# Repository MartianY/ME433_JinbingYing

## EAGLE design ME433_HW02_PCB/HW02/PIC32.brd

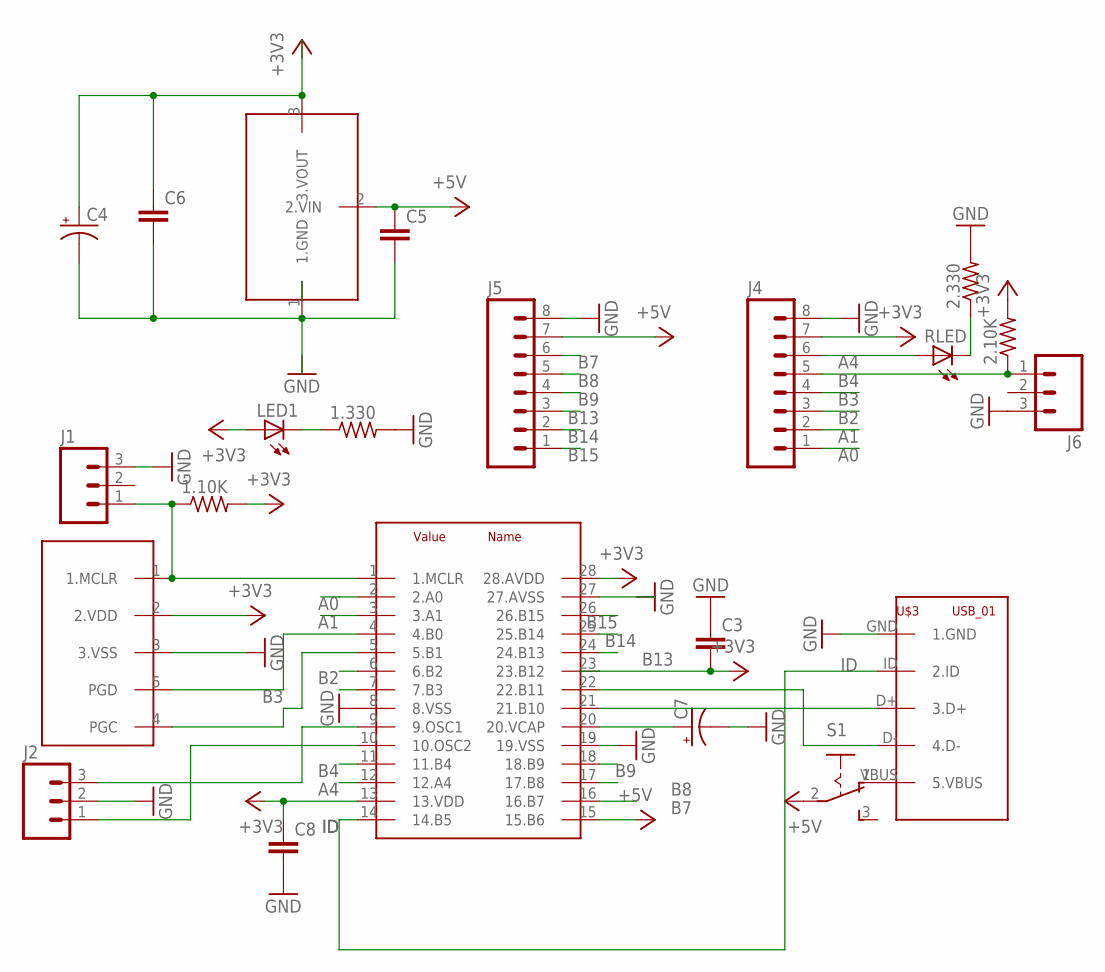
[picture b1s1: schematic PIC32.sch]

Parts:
1.10K, 1.330, 2.10K, 2.330: R-US_0207/10; 0207/10
C3, C5, C6, C8: C5/3; C5B3
C4, C7: CPOL-USB45181B; B45181B
J1, J2, J6: M03PTH; 1X03
J4, J5: M08; 1X08_ROUND
LED1: LED3MM
RLED: LED3MM
S1: 255SB
U$1: PIC28; DIL28-3
U$2: MCP1702; TO92
U$3: USB_01; USB-MB-H
U$5: SWITCH_M05; 1X05

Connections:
+3V3: 1.10K.2, 2.10K.2, C3.2, C8.1, J4.7, LED1.A, U$1.13 (13.VDD), U$1.23 (23.B12), U$1.28 (28.AVDD), U$5.2 (2.VDD)
+5V: C5.1, J5.7, S1.2, U$1.15 (15.B6), U$2.2 (2.VIN)
A0: J4.1, U$1.2 (2.A0)
A1: J4.2, U$1.3 (3.A1)
A4: J4.6, RLED.A, U$1.12 (12.A4)
B2: J4.3, U$1.6 (6.B2)
B3: J4.4, U$1.7 (7.B3)
B4: 2.10K.1, J4.5, J6.1, U$1.11 (11.B4)
B7: J5.6, U$1.16 (16.B7)
B8: J5.5, U$1.17 (17.B8)
B9: J5.4, U$1.18 (18.B9)
B13: J5.3, U$1.24 (24.B13)
B14: J5.2, U$1.25 (25.B14)
B15: J5.1, U$1.26 (26.B15)
GND: 1.330.2, 2.330.2, C3.1, C7.-, C8.2, J1.3, J2.2, J4.8, J5.8, J6.3, U$1.8 (8.VSS), U$1.19 (19.VSS), U$3.GND (1.GND), U$5.3 (3.VSS)
ID: U$1.14 (14.B5), U$3.ID (2.ID)
unnamed: S1.1 (O), U$3.VBUS (5.VBUS)
unnamed: C4.-, C5.2, C6.2, U$2.1 (1.GND)
unnamed: C4.+, C6.1, U$2.3 (3.VOUT)
unnamed: U$1.5 (5.B1), U$5.4 (PGC)
unnamed: U$1.4 (4.B0), U$5.5 (PGD)
unnamed: J2.3, U$1.9 (9.OSC1)
unnamed: J2.1, U$1.10 (10.OSC2)
unnamed: C7.+, U$1.20 (20.VCAP)
unnamed: U$1.22 (22.B11), U$3.D- (4.D-)
unnamed: U$1.21 (21.B10), U$3.D+ (3.D+)
unnamed: 1.330.1, LED1.K (C)
unnamed: 1.10K.1, J1.1, U$1.1 (1.MCLR), U$5.1 (1.MCLR)
unnamed: 2.330.1, RLED.K (C)

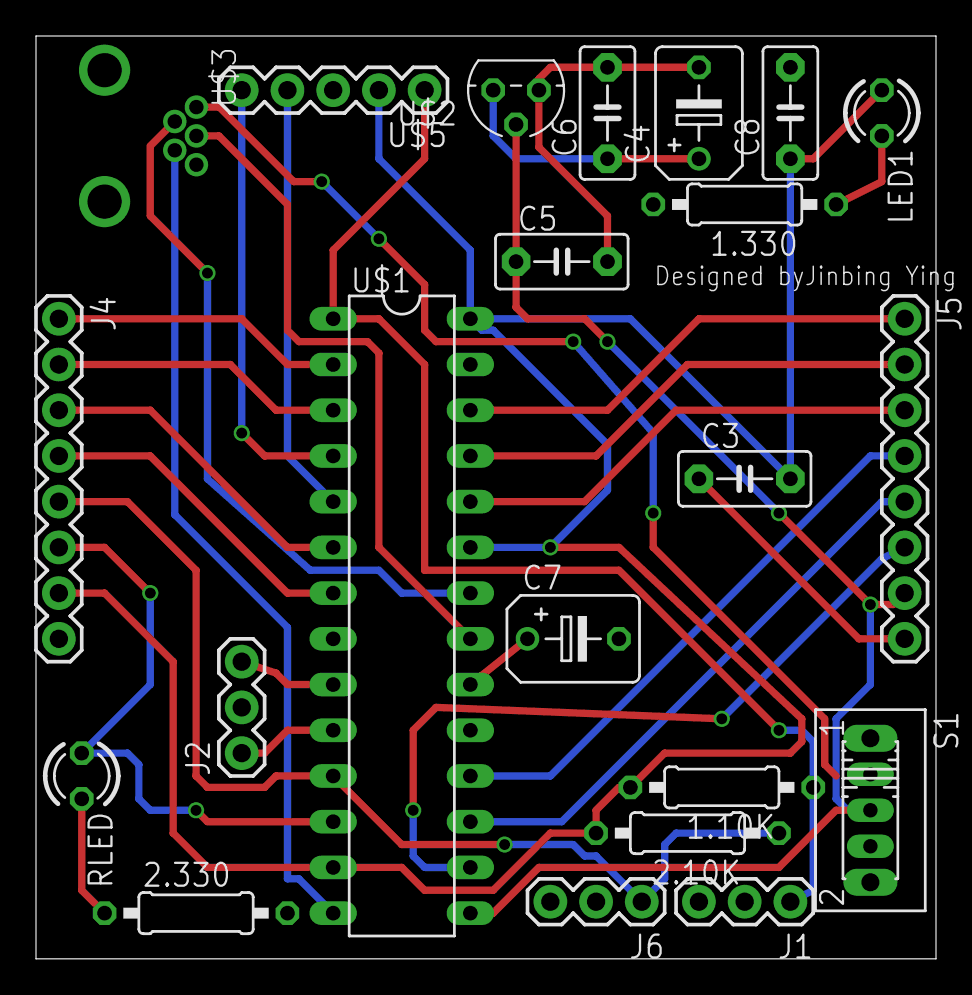
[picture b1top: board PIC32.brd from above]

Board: 2 copper layers, 50.0 x 51.3 mm, 22 parts (0 on the bottom side), 29 nets.

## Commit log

2016-05-31 Organized
2016-05-31 edit
2016-05-31 Edit
    Check
2016-06-02 Update Camera
